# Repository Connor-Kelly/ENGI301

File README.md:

# ENGI301
Repository for ENGI301 course work

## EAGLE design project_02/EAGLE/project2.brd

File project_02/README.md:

# PCB Design
This folder contains the data needed to make a music_box pcb. 
Built for the following project: https://www.hackster.io/connorkelly726/music-box-49702b

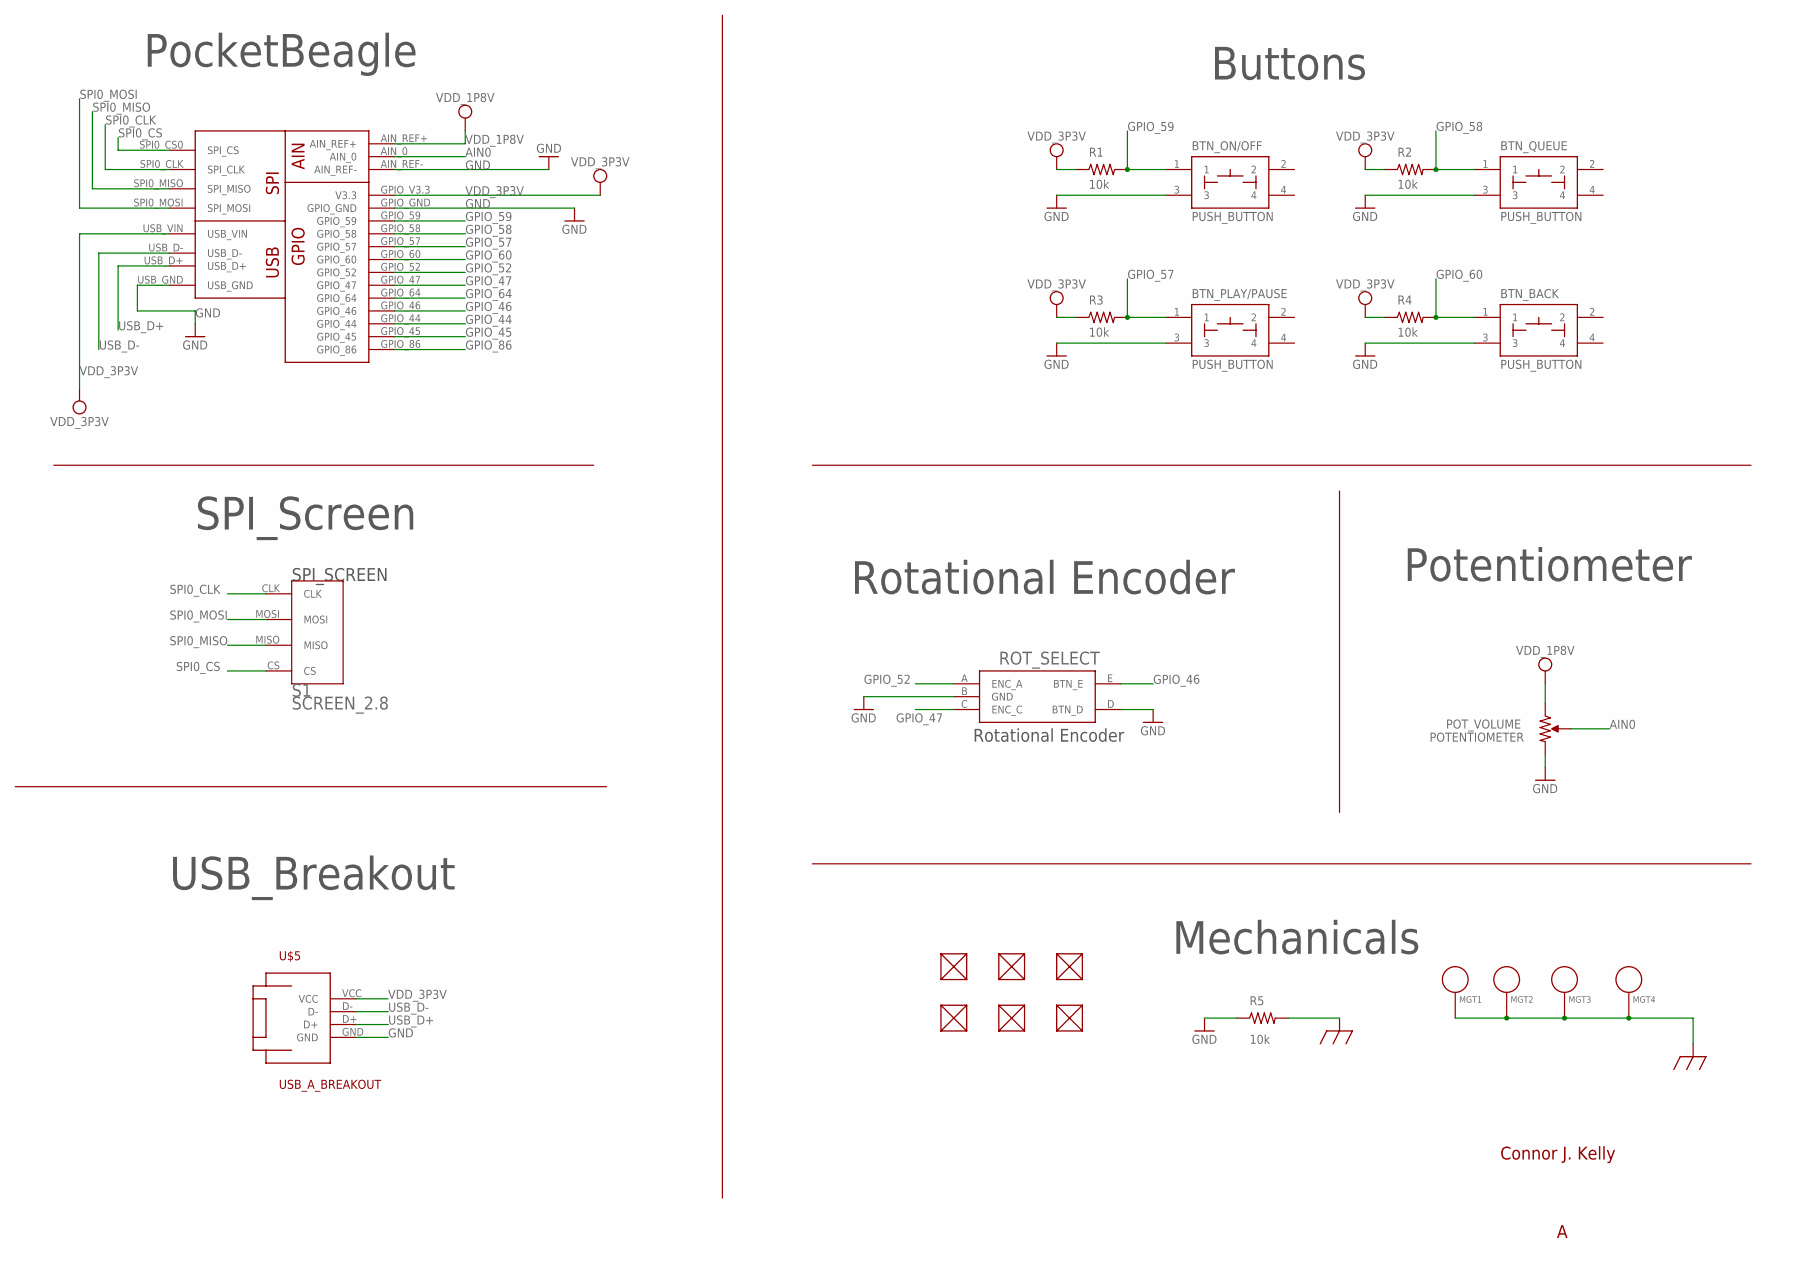
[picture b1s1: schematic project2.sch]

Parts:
BTN_BACK: PUSH_BUTTON; BUTTON_12.5MM
BTN_ON/OFF: PUSH_BUTTON; BUTTON_12.5MM
BTN_PLAY/PAUSE: PUSH_BUTTON; BUTTON_12.5MM
BTN_QUEUE: PUSH_BUTTON; BUTTON_12.5MM
FUD1, FUD2, FUD3, FUD4, FUD5, FUD6: FIDUCIAL; FIDUCIAL_40MIL
MGT1, MGT2, MGT3, MGT4: MOUNTING_HOLE
POT_VOLUME: POTENTIOMETER; POT-PO90S
R1, R2, R3, R4, R5: 10k; R0402
ROT_SELECT: PEC16-4015F-S0024
S1: SCREEN_2.8
U$3: POCKETBEAGLE
U$5: USB_A_BREAKOUT

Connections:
AIN0: POT_VOLUME.S, U$3.AIN_0
CGND: MGT1.P$1, MGT2.P$1, MGT3.P$1, MGT4.P$1, R5.2
GND: BTN_BACK.3, BTN_ON/OFF.3, BTN_PLAY/PAUSE.3, BTN_QUEUE.3, POT_VOLUME.CW, R5.1, ROT_SELECT.B (GND), ROT_SELECT.D (BTN_D), U$3.AIN_REF-, U$3.GPIO_GND, U$3.USB_GND, U$5.GND
GPIO_44: U$3.GPIO_44
GPIO_45: U$3.GPIO_45
GPIO_46: ROT_SELECT.E (BTN_E), U$3.GPIO_46
GPIO_47: ROT_SELECT.C (ENC_C), U$3.GPIO_47
GPIO_52: ROT_SELECT.A (ENC_A), U$3.GPIO_52
GPIO_57: BTN_PLAY/PAUSE.1, R3.2, U$3.GPIO_57
GPIO_58: BTN_QUEUE.1, R2.2, U$3.GPIO_58
GPIO_59: BTN_ON/OFF.1, R1.2, U$3.GPIO_59
GPIO_60: BTN_BACK.1, R4.2, U$3.GPIO_60
GPIO_64: U$3.GPIO_64
GPIO_86: U$3.GPIO_86
SPI0_CLK: S1.CLK, U$3.SPI0_CLK (SPI_CLK)
SPI0_CS: S1.CS, U$3.SPI0_CS0 (SPI_CS)
SPI0_MISO: S1.MISO, U$3.SPI0_MISO (SPI_MISO)
SPI0_MOSI: S1.MOSI, U$3.SPI0_MOSI (SPI_MOSI)
USB_D+: U$3.USB_D+, U$5.D+
USB_D-: U$3.USB_D-, U$5.D-
VDD_1P8V: POT_VOLUME.CCW, U$3.AIN_REF+
VDD_3P3V: R1.1, R2.1, R3.1, R4.1, U$3.GPIO_V3.3 (V3.3), U$3.USB_VIN, U$5.VCC

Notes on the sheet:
Buttons
Rotational Encoder
Potentiometer
Mechanicals
USB_Breakout
SPI_Screen
PocketBeagle
Connor J. Kelly

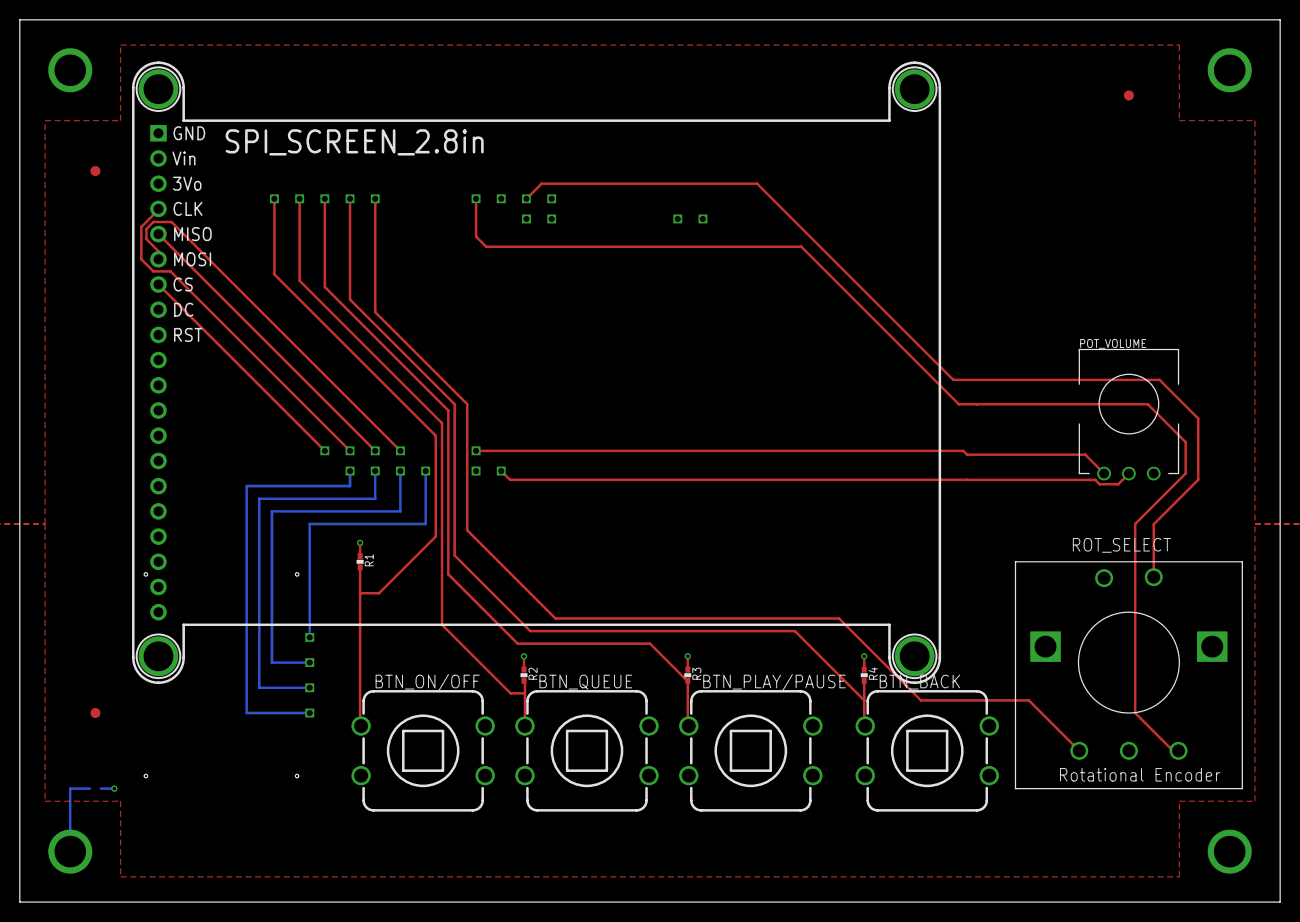
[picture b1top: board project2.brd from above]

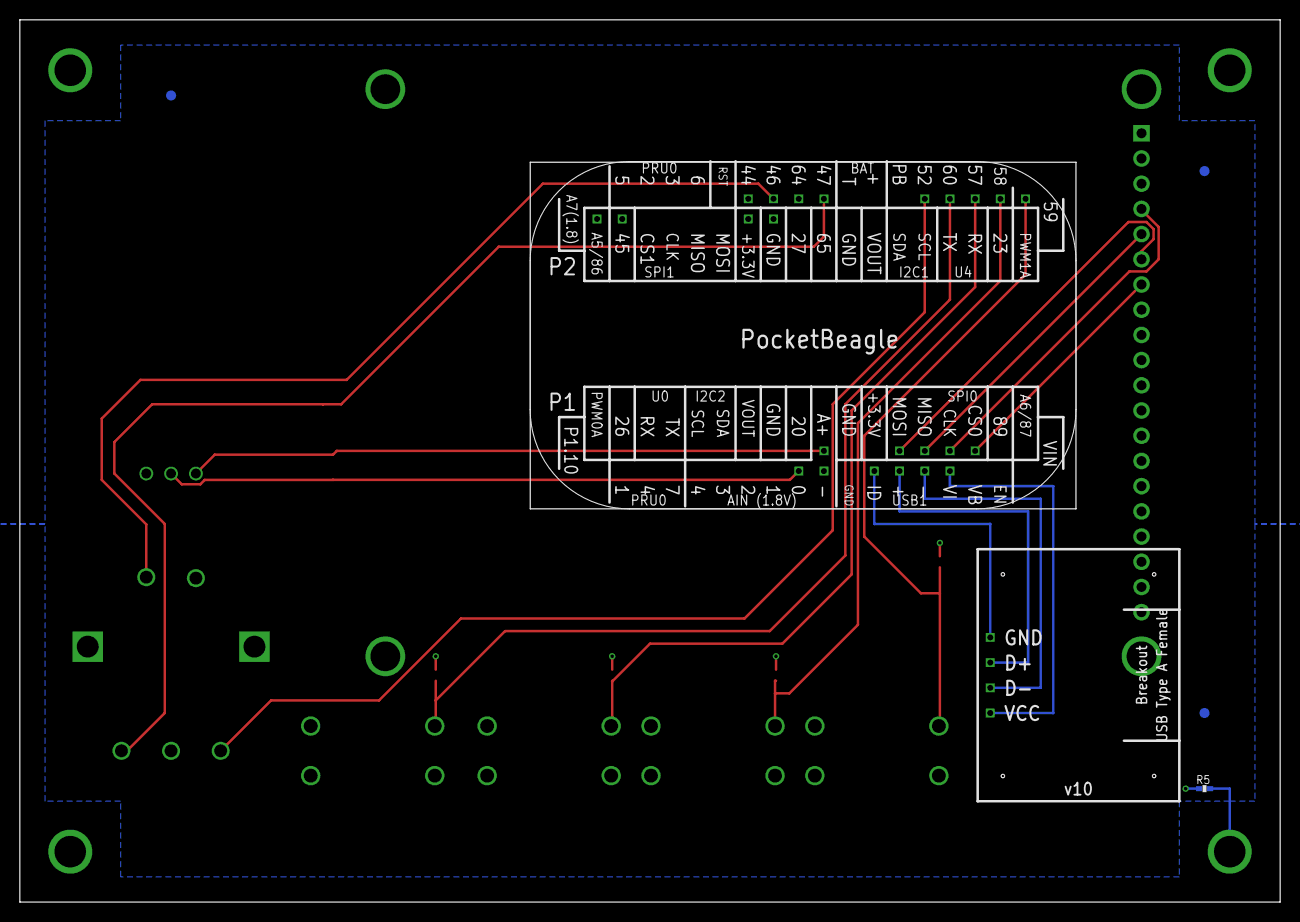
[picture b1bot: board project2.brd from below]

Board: 4 copper layers, 127.0 x 88.9 mm, 24 parts (7 on the bottom side), 18 nets.

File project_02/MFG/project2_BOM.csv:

Qty,Value,Device,Package,Parts,Description,DESCRIPTION,MF,MP,PURCHASE-URL
5,10k,R_R0402,R0402,"R1, R2, R3, R4, R5","RESISTOR, American symbol",,Bournes Inc,,
6,FIDUCIAL,FIDUCIAL,FIDUCIAL_40MIL,"FUD1, FUD2, FUD3, FUD4, FUD5, FUD6",,,N/A,,
4,MOUNTING_HOLE,MOUNTING_HOLE,MOUNTING_HOLE,"MGT1, MGT2, MGT3, MGT4",Chassis Mounting Hole w/GND connection ability,,N/A,,
1,PEC16-4015F-S0024,PEC16-4015F-S0024,PEC16-4015F-S0024,ROT_SELECT,Mechanical Encoder Rotary Incremental Flat 0.02N.m Straight Quadrature Digital Square Wave 24PPR Through Hole PC Pin, Mechanical Encoder Rotary Incremental Flat 0.02N.m Straight Quadrature Digital Square Wave 24PPR Through Hole PC Pin ,Bourns,PEC16-4015F-S0024,https://pricing.snapeda.com/search/part/PEC16-4015F-S0024/?ref=eda
1,POCKETBEAGLE,POCKETBEAGLE,POCKETBEAGLE,U$3,PocketBeagle is an ultra-tiny-yet-complete open-source USB-key-fob computer.,,BeagleBoard,,
1,POTENTIOMETER,POTENTIOMETER,POT-PO90S,POT_VOLUME,"10k Ohm 1 Gang Linear Through Hole Potentiometer Detent 1.0 Kierros Conductive Plastic 0.03W, 1/32W PC Pins, Board Locks",,TT Electronics/BI,,
4,PUSH_BUTTON,PUSH_BUTTON,BUTTON_12.5MM,"BTN_BACK, BTN_ON/OFF, BTN_PLAY/PAUSE, BTN_QUEUE",Momentary Press Button Switch,,Adafruit,,
1,SCREEN_2.8,SCREEN_2.8,SCREEN_2.8,S1,"SPI Screen, TFT, 2.8in",,Adafruit,,
1,USB_A_BREAKOUT,USB_A_BREAKOUT,USB_A_BREAKOUT,U$5,USB Breakout Board,,SparkFun,,

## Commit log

2023-02-13 Added python files from A4
2023-02-13 tested on-board, all working
2023-02-13 removed duplicate calc.py
2023-02-14 Updated Proposal
2023-02-16 added things
2023-02-22 added
2023-02-22 got segment display working
2023-03-05 added sample muisc
2023-03-07 updated swb and docs
2023-03-07 updated proposal with Software and GUI diagrams
2023-03-30 pushed from beagle
2023-03-30 push from computer
2023-04-02 added smoke music
2023-04-02 added sample directory
2023-04-02 updated smoke
2023-04-02 created mocp class
2023-04-02 updated moc
2023-04-02 laptop push, created m3u.ipynb to prototype playlist parsing
2023-04-02 push from vm
2023-04-04 added ipynb files
2023-04-04 commit from beagle, added most files in project dir
2023-04-04 updated mocp
2023-04-04 added images for docs
2023-04-04 organized files
2023-04-04 updated readme and docs
2023-04-05 moved directories around
2023-04-21 created project1 subfolder and new folder for project2
2023-05-03 added pcb things
